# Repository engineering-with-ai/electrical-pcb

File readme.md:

# [electrical-pcb] ⚡

CM4 carrier board — Raspberry Pi Compute Module 4 carrier for an outdoor self-contained sensor system with computer vision, thermal imaging, cellular uplink, and solar + battery power. 5V screw terminal input, polyfuse + reverse polarity protection, CP2102N USB-UART debug, MAX3485 RS-485, I2C/SPI/GPIO headers on 2.54mm pitch, 100x80mm 2-layer board.

Foundation board that exposes raw CM4 interfaces via headers. Downstream boards connect RGB camera (CSI), FLIR Lepton thermal sensor (SPI), cellular modem (RS-485 Modbus), and solar charge controller (I2C BMS telemetry).

**[View generated deliverables](output/)**

## 📋 Board Spec

```mermaid
graph LR
    PWR["5V Screw Terminal"] --> FUSE["Polyfuse<br/>1812L200 2A"]
    FUSE --> FET["SI2301 P-FET<br/>Reverse Polarity"]
    FET --> RAIL["5V_RAIL"]
    RAIL --> CM4["CM4 Module<br/>Hirose DF40"]
    CM4 --> UART["CP2102N<br/>USB-UART Debug"]
    CM4 --> RS485["MAX3485<br/>RS-485"]
    CM4 --> I2C["I2C Header<br/>2.2k Pull-ups"]
    CM4 --> SPI["SPI Header"]
    CM4 --> GPIO["GPIO Header"]

    style PWR fill:#4a9,stroke:#333
    style FUSE fill:#a94,stroke:#333
    style FET fill:#a94,stroke:#333
    style RAIL fill:#4a9,stroke:#333
    style CM4 fill:#49a,stroke:#333
    style UART fill:#94a,stroke:#333
    style RS485 fill:#94a,stroke:#333
    style I2C fill:#94a,stroke:#333
    style SPI fill:#94a,stroke:#333
    style GPIO fill:#94a,stroke:#333
```

## 🔄 Workflow

```
theory.ipynb (sympy + pint) -> cad/model.py (SKiDL -> netlist) -> sim/ (power + signal integrity) -> pytest (assert vs theory)
```

1. `theory.ipynb` derives power rail budget, polyfuse margin, I2C pull-up selection, RS-485 bias
2. `cad/model.py` defines circuit in SKiDL, generates KiCad netlist
3. `sim/model.py` validates power rail voltage, I2C rise time, RS-485 bias
4. `sim/test_run.py` asserts simulation matches theory within tolerance
5. `/generate-schematic` generates professional `.kicad_sch` from netlist + `layout_spec.yaml`

## 🚀 Quick Start

```bash
uv sync
uv run poe checks          # black + ruff lint
uv run poe notebook         # execute theory.ipynb
uv run poe build            # SKiDL -> KiCad netlist + schematic
uv run poe sim              # 4/4 tests pass
```

## 🏭 Code to Fabrication

Everything is CLI or Claude skill except 3 manual steps marked with a wrench.

```
 1. uv run poe build                 → SKiDL netlist + schematic
 2. uv run poe sim                   → 4/4 tests pass
 3. /generate-schematic              → professional .kicad_sch
 4. uv run poe validate-model        → ERC 0 errors
 5. uv run poe generate-model        → schematic SVG + dark SVG + drawing PDF

    ┌──────────────────────────────────────────────────────┐
    │  HUMAN : open pcbnew, press F8, save, close          │
    └──────────────────────────────────────────────────────┘

 6. /layout-pcb                      → place + autoroute + ground pour + DRC + review SVG

    ┌──────────────────────────────────────────────────────┐
    │  HUMAN: review SVG, tweak pcb_placement.yaml, re-run │
    └──────────────────────────────────────────────────────┘

 7. uv run poe validate-asm          → DRC 0 errors
 8. uv run poe generate-asm          → gerbers + BOM + CPL + STEP
```

## 📁 Structure

- `theory.ipynb` — power budget + signal integrity derivation
- `sim/` — simulation + pytest assertions against theory
- `cad/netlist/` — SKiDL circuit definition (model.py, power.py, comms.py, io_headers.py)
- `cad/layout_spec.yaml` — schematic layout + block definitions
- `cad/pcb_placement.yaml` — AI-generated PCB component positions
- `cad/drawing-sheet.kicad_wks` — custom EWAI title block
- `cad/drawing/` — SVG dark mode conversion, PCB placement script
- `output/drawings/` — schematic SVGs (light + dark), drawing PDF
- `output/gerbers/` — fabrication gerbers + drill files
- `output/fab/` — BOM, CPL for assembly

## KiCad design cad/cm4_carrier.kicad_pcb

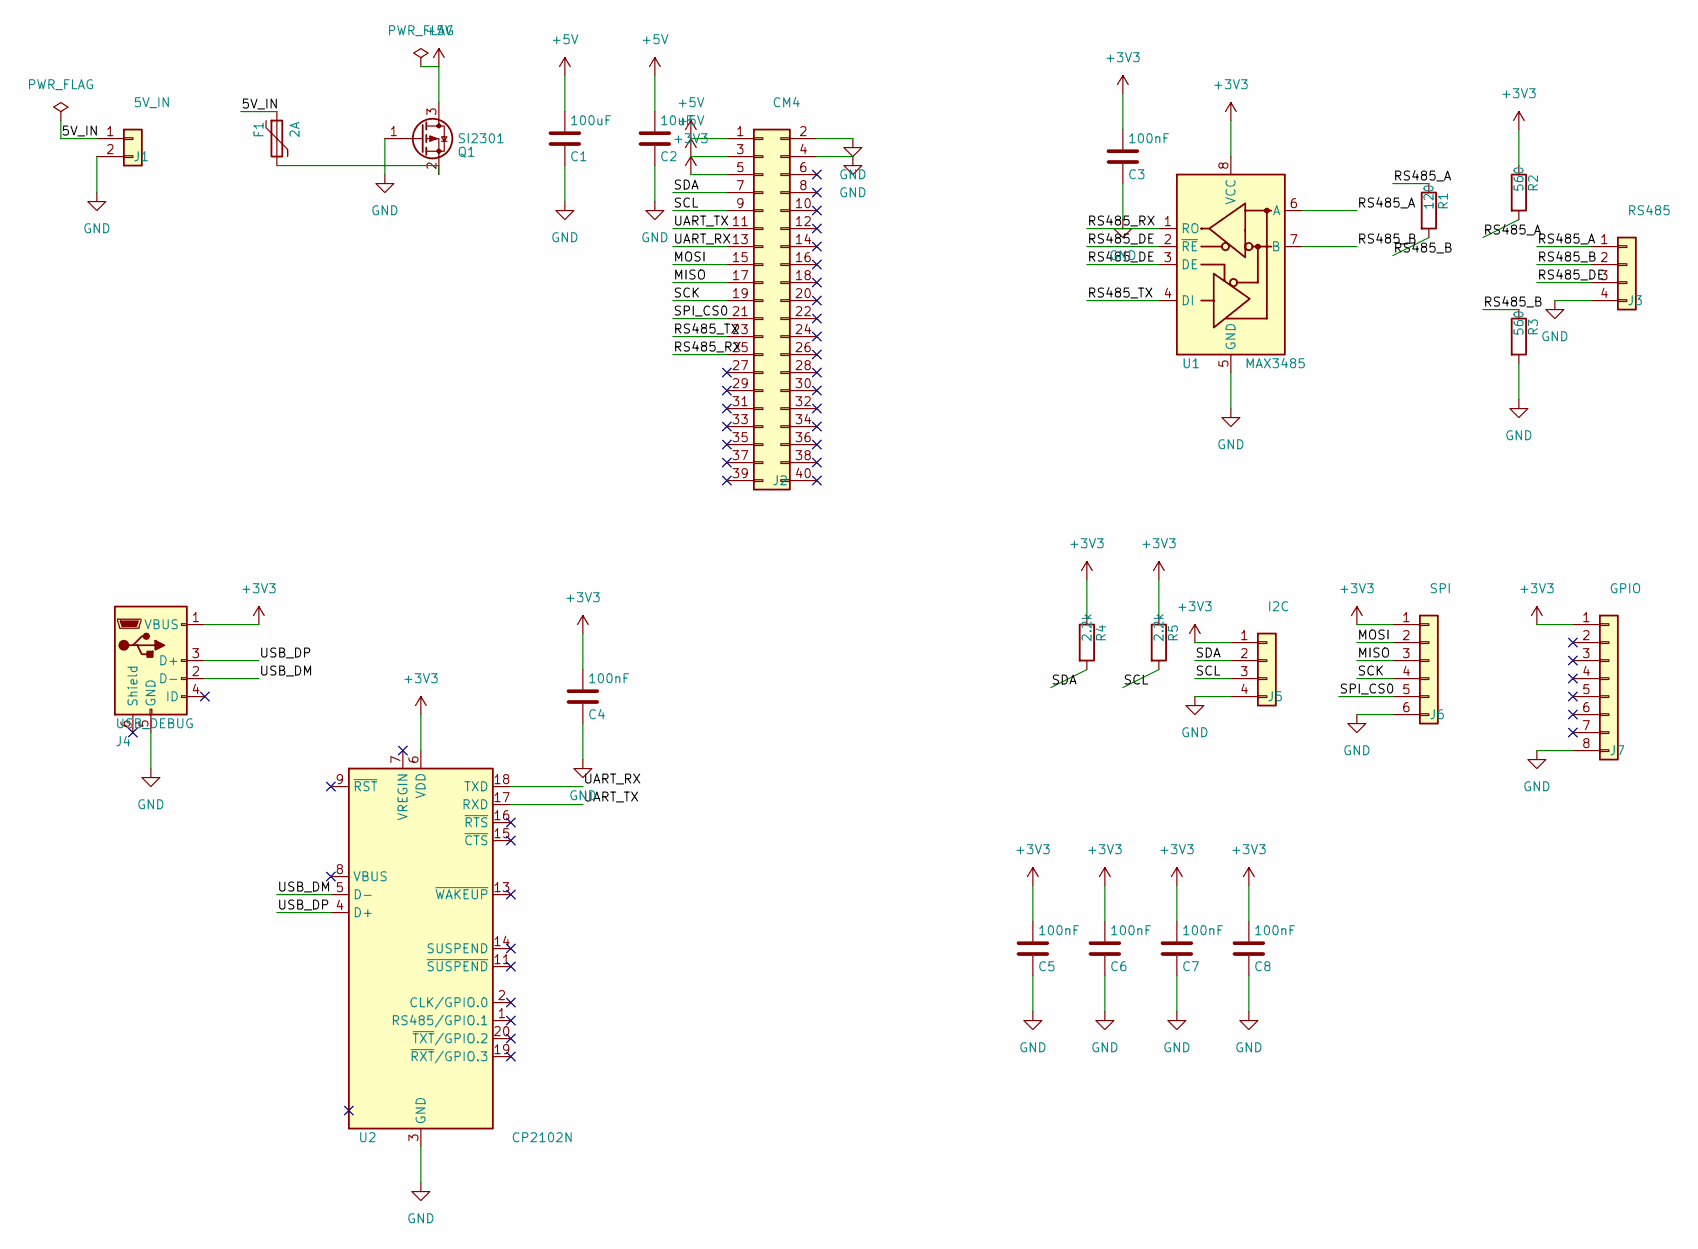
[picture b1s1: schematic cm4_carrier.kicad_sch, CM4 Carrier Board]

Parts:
C1: 100uF; C_1210_3225Metric
C2: 10uF; C_0805_2012Metric
C3, C4, C5, C6, C7, C8: 100nF; C_0402_1005Metric
F1: 2A; Fuse_1812_4532Metric
J1: 5V_IN; PinHeader_1x02_P2.54mm_Vertical
J2: CM4; PinHeader_2x20_P2.54mm_Vertical
J3: RS485; PinHeader_1x04_P2.54mm_Vertical
J4: USB_DEBUG; USB_Micro-B_Molex_47346-0001
J5: I2C; PinHeader_1x04_P2.54mm_Vertical
J6: SPI; PinHeader_1x06_P2.54mm_Vertical
J7: GPIO; PinHeader_1x08_P2.54mm_Vertical
Q1: SI2301; SOT-23
R1: 120; R_0805_2012Metric
R2, R3: 560; R_0603_1608Metric
R4, R5: 2.2k; R_0603_1608Metric
U1: MAX3485; SOIC-8_3.9x4.9mm_P1.27mm
U2: CP2102N; QFN-20-1EP_4x4mm_P0.5mm_EP2.5x2.5mm

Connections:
+3V3: C3.1, C4.1, C5.1, C6.1, C7.1, C8.1, J2.5, J4.1 (VBUS), J5.1, J6.1, J7.1, R2.1, R4.1, R5.1, U1.8 (VCC), U2.6 (VDD)
+5V: C1.1, C2.1, J2.1, J2.3, Q1.3 (D)
/5V_IN: F1.1, J1.1
/MISO: J2.17, J6.3
/MOSI: J2.15, J6.2
/RS485_A: J3.1, R1.1, R2.2, U1.6 (A)
/RS485_B: J3.2, R1.2, R3.1, U1.7 (B)
/RS485_DE: J3.3, U1.2 (~RE), U1.3 (DE)
/RS485_RX: J2.25, U1.1 (RO)
/RS485_TX: J2.23, U1.4 (DI)
/SCK: J2.19, J6.4
/SCL: J2.9, J5.3, R5.2
/SDA: J2.7, J5.2, R4.2
/SPI_CS0: J2.21, J6.5
/UART_RX: J2.13, U2.18 (TXD)
/UART_TX: J2.11, U2.17 (RXD)
/USB_DM: J4.2 (D-), U2.5 (D-)
/USB_DP: J4.3 (D+), U2.4 (D+)
GND: C1.2, C2.2, C3.2, C4.2, C5.2, C6.2, C7.2, C8.2, J1.2, J2.2, J2.4, J3.4, J4.5 (GND), J5.4, J6.6, J7.8, Q1.1 (G), R3.2, U1.5 (GND), U2.3 (GND), U2.12 (GND), U2.21 (GND)
unnamed: F1.2, Q1.2 (S)

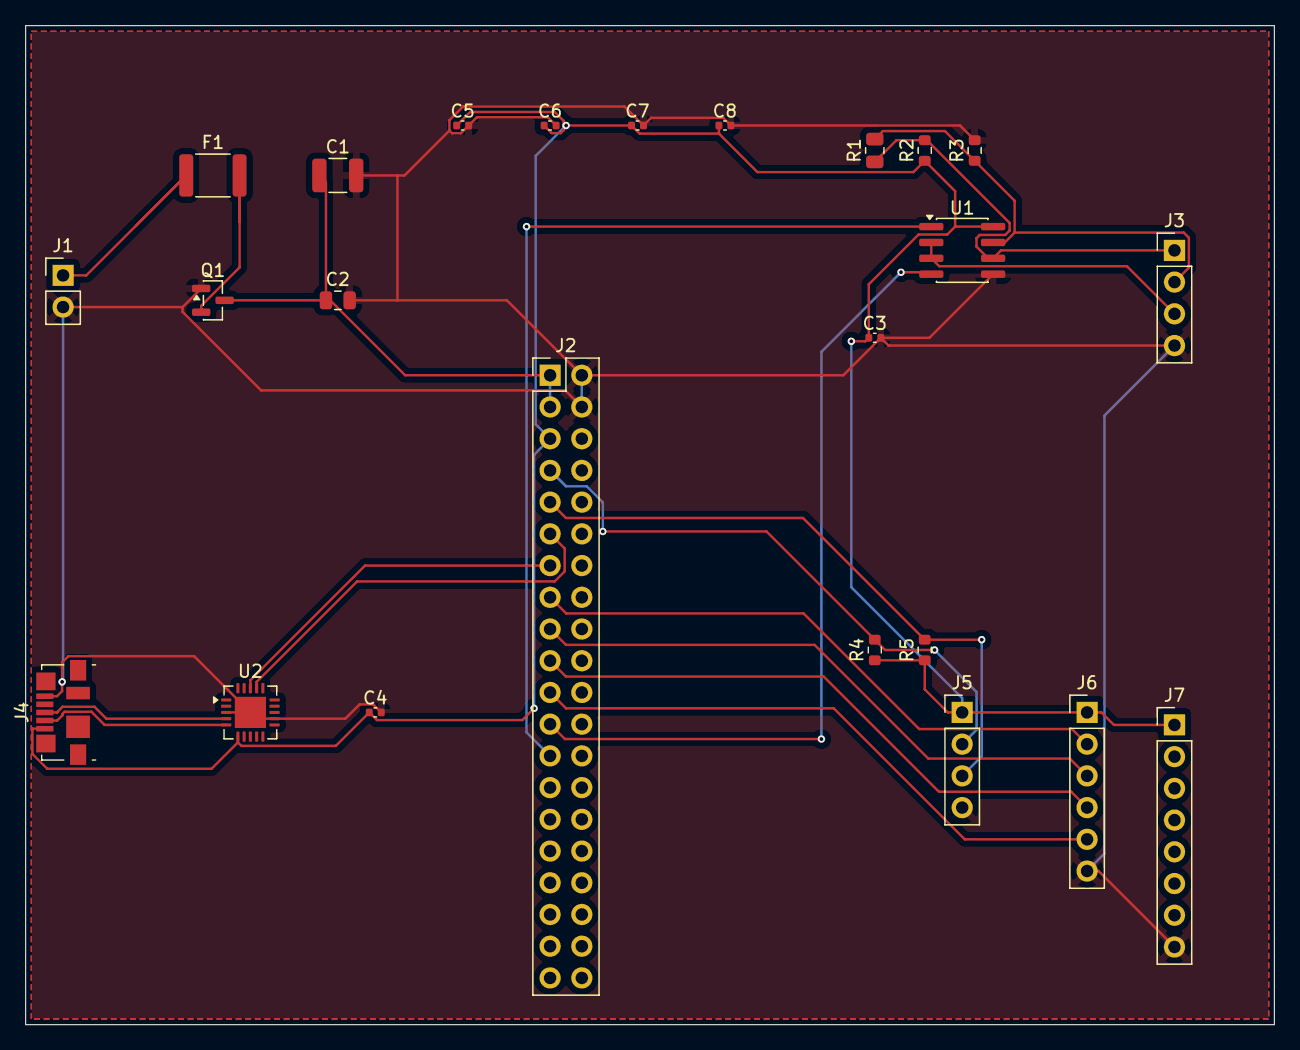
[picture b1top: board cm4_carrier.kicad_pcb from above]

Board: 2 copper layers, 100.0 x 80.0 mm, 24 parts (0 on the bottom side), 20 nets.

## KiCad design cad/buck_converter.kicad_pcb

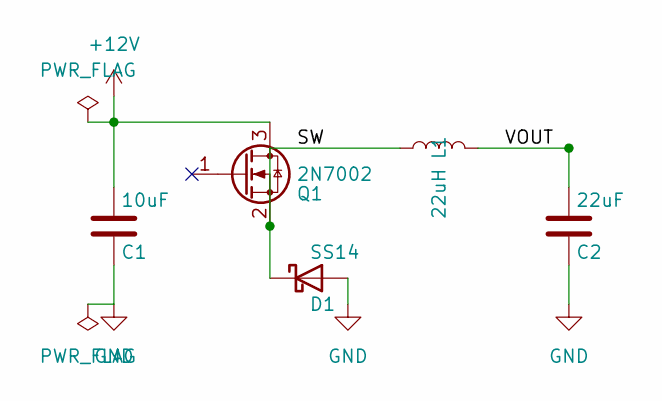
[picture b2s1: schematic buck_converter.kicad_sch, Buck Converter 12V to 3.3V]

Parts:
C1: 10uF; C_0805_2012Metric
C2: 22uF; C_0805_2012Metric
D1: SS14; D_SOD-123
L1: 22uH; L_1210_3225Metric
Q1: 2N7002; SOT-23

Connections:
+12V: C1.1, Q1.3 (D)
/SW: D1.1 (K), L1.1, Q1.2 (S)
/VOUT: C2.1, L1.2
GND: C1.2, C2.2, D1.2 (A)

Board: 2 copper layers, 5 parts (0 on the bottom side), 4 nets, no tracks yet.

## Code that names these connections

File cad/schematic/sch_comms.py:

"""Communication blocks: RS-485 (MAX3485) and USB-UART (CP2102N)."""

from cad.schematic.sch_helpers import (
    CP2102N_PINS,
    MAX3485_PINS,
    USB_MICRO_PINS,
    c_pin,
    conn_1xn_pin,
    ic_pin,
    nc,
    r_pin,
    stub_label,
    stub_pwr,
)

FP_SOIC8 = "Package_SO:SOIC-8_3.9x4.9mm_P1.27mm"
FP_R_0805 = "Resistor_SMD:R_0805_2012Metric"
FP_R_0603 = "Resistor_SMD:R_0603_1608Metric"
FP_CONN_1X04 = "Connector_PinHeader_2.54mm:PinHeader_1x04_P2.54mm_Vertical"
FP_C_0402 = "Capacitor_SMD:C_0402_1005Metric"
FP_QFN20 = "Package_DFN_QFN:QFN-20-1EP_4x4mm_P0.5mm_EP2.5x2.5mm"
FP_USB_MICRO = "Connector_USB:USB_Micro-B_Molex_47346-0001"


def place_rs485_block(sch, bx: int, by: int, pwr: dict) -> None:
    """Place RS-485 transceiver block."""
    u1_pos = (bx + 22, by + 20)
    u1 = sch.components.add("Interface_UART:MAX3485", "U1", "MAX3485", position=u1_pos)
    u1.footprint = FP_SOIC8

    stub_label(sch, ic_pin(u1_pos, MAX3485_PINS, 1), "RS485_RX", dx=-8)
    stub_label(sch, ic_pin(u1_pos, MAX3485_PINS, 2), "RS485_DE", dx=-8)
    stub_label(sch, ic_pin(u1_pos, MAX3485_PINS, 3), "RS485_DE", dx=-8)
    stub_label(sch, ic_pin(u1_pos, MAX3485_PINS, 4), "RS485_TX", dx=-8)
    stub_pwr(sch, ic_pin(u1_pos, MAX3485_PINS, 8), "power:+3V3", pwr, dy=-4)
    stub_pwr(sch, ic_pin(u1_pos, MAX3485_PINS, 5), "power:GND", pwr, dy=4)
    stub_label(sch, ic_pin(u1_pos, MAX3485_PINS, 6), "RS485_A", dx=6, rotation=180)
    stub_label(sch, ic_pin(u1_pos, MAX3485_PINS, 7), "RS485_B", dx=6, rotation=180)

    r1_pos = (bx + 44, by + 14)
    r1 = sch.components.add("Device:R", "R1", "120", position=r1_pos)
    r1.footprint = FP_R_0805
    stub_label(sch, r_pin(r1_pos, 2), "RS485_A", dx=-4)
    stub_label(sch, r_pin(r1_pos, 1), "RS485_B", dx=-4, dy=2)

    r2_pos = (bx + 54, by + 12)
    r2 = sch.components.add("Device:R", "R2", "560", position=r2_pos)
    r2.footprint = FP_R_0603
    stub_pwr(sch, r_pin(r2_pos, 2), "power:+3V3", pwr, dy=-4)
    stub_label(sch, r_pin(r2_pos, 1), "RS485_A", dx=-4, dy=2)

    r3_pos = (bx + 54, by + 28)
    r3 = sch.components.add("Device:R", "R3", "560", position=r3_pos)
    r3.footprint = FP_R_0603
    stub_label(sch, r_pin(r3_pos, 2), "RS485_B", dx=-4)
    stub_pwr(sch, r_pin(r3_pos, 1), "power:GND", pwr, dy=4)

    j3_pos = (bx + 66, by + 20)
    j3 = sch.components.add(
        "Connector_Generic:Conn_01x04", "J3", "RS485", position=j3_pos
    )
    j3.footprint = FP_CONN_1X04
    stub_label(sch, conn_1xn_pin(j3_pos, 4, 1), "RS485_A", dx=-6)
    stub_label(sch, conn_1xn_pin(j3_pos, 4, 2), "RS485_B", dx=-6)
    stub_label(sch, conn_1xn_pin(j3_pos, 4, 3), "RS485_DE", dx=-6)
    stub_pwr(sch, conn_1xn_pin(j3_pos, 4, 4), "power:GND", pwr, dx=-4, dy=0)

    c3_pos = (bx + 10, by + 8)
    c3 = sch.components.add("Device:C", "C3", "100nF", position=c3_pos)
    c3.footprint = FP_C_0402
    stub_pwr(sch, c_pin(c3_pos, 1), "power:+3V3", pwr, dy=-4)
    stub_pwr(sch, c_pin(c3_pos, 2), "power:GND", pwr, dy=4)


def place_usb_uart_block(sch, bx: int, by: int, pwr: dict) -> None:
    """Place USB-UART bridge block."""
    # Reason: y-offset +40 avoids J4.GND and U2.TXD sharing exact y-coordinate
    u2_pos = (bx + 36, by + 40)
    u2 = sch.components.add(
        "Interface_USB:CP2102N-Axx-xQFN20", "U2", "CP2102N", position=u2_pos
    )
    u2.footprint = FP_QFN20

    stub_pwr(sch, ic_pin(u2_pos, CP2102N_PINS, 6), "power:+3V3", pwr, dy=-4)
    stub_pwr(sch, ic_pin(u2_pos, CP2102N_PINS, 3), "power:GND", pwr, dy=4)
    stub_label(sch, ic_pin(u2_pos, CP2102N_PINS, 4), "USB_DP", dx=-6)
    stub_label(sch, ic_pin(u2_pos, CP2102N_PINS, 5), "USB_DM", dx=-6)
    stub_label(sch, ic_pin(u2_pos, CP2102N_PINS, 17), "UART_TX", dx=8, rotation=180)
    stub_label(sch, ic_pin(u2_pos, CP2102N_PINS, 18), "UART_RX", dx=8, rotation=180)

    used = {3, 4, 5, 6, 12, 17, 18, 21}
    for pin_num in range(1, 22):
        if pin_num not in used:
            nc(sch, ic_pin(u2_pos, CP2102N_PINS, pin_num))

    j4_pos = (bx + 6, by + 8)
    j4 = sch.components.add("Connector:USB_B_Micro", "J4", "USB_DEBUG", position=j4_pos)
    j4.footprint = FP_USB_MICRO

    stub_pwr(sch, ic_pin(j4_pos, USB_MICRO_PINS, 1), "power:+3V3", pwr, dx=6, dy=0)
    stub_label(sch, ic_pin(j4_pos, USB_MICRO_PINS, 3), "USB_DP", dx=6, rotation=180)
    stub_label(sch, ic_pin(j4_pos, USB_MICRO_PINS, 2), "USB_DM", dx=6, rotation=180)
    stub_pwr(sch, ic_pin(j4_pos, USB_MICRO_PINS, 5), "power:GND", pwr, dy=4)
    nc(sch, ic_pin(j4_pos, USB_MICRO_PINS, 4))
    nc(sch, ic_pin(j4_pos, USB_MICRO_PINS, 6))

    c4_pos = (bx + 54, by + 12)
    c4 = sch.components.add("Device:C", "C4", "100nF", position=c4_pos)
    c4.footprint = FP_C_0402
    stub_pwr(sch, c_pin(c4_pos, 1), "power:+3V3", pwr, dy=-4)
    stub_pwr(sch, c_pin(c4_pos, 2), "power:GND", pwr, dy=4)

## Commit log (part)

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2026-03-12 init
2026-03-12 add mkdir sim/results to CI
